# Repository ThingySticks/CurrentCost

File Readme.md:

Connect Photon/Electron to a CurrentCost unit via the RJ45 interface underneat and replace the NetSmart

Pin outs:

1 Vcc supply
4 GND
7 EnviR Unit Rx Data
8 EnviR Unit Tx Data

Data:

<msg>          
   <src>CC128-v0.11</src> 
   <dsb>00089</dsb>     
   <time>13:02:39</time>     
   <tmpr>18.7</tmpr>        
   <sensor>1</sensor>     
   <id>01234</id>                
   <type>1</type>              
   <ch1>
      <watts>00345</watts>
   </ch1>
   <ch2>
      <watts>02151</watts>
   </ch2>
   <ch3>
      <watts>00000</watts>
   </ch3>
</msg>

Expected Serial interface:

 baudrate: 57600,
  dataBits: 8,
  parity: 'none',
  stopBits: 1

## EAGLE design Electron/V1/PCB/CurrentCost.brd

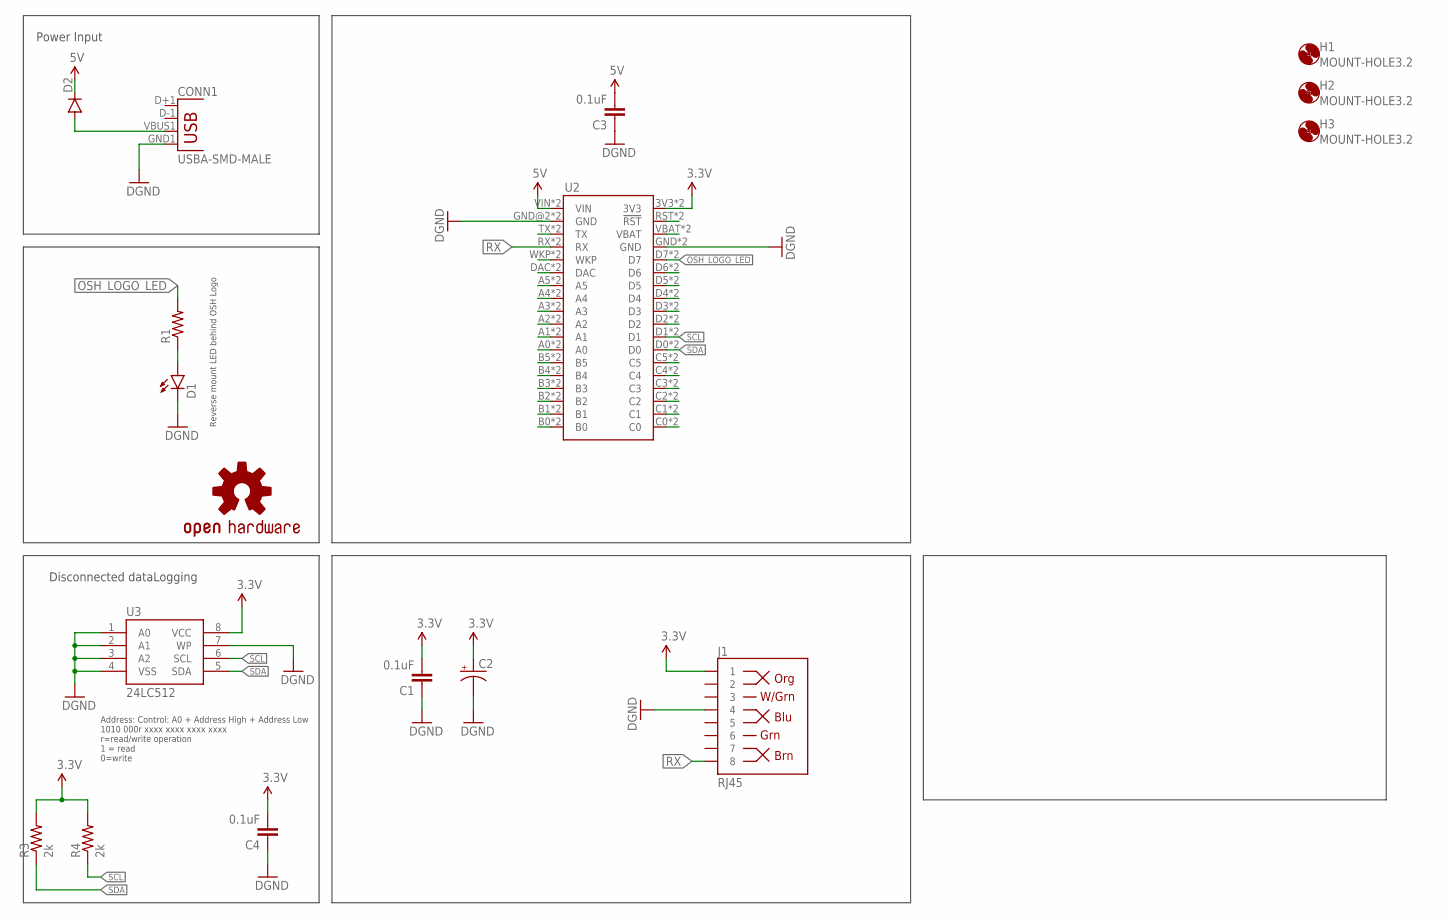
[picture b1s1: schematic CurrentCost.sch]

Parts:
C1, C3, C4: 0.1uF; 0805
C2: CAP_POLPTH1; CPOL-RADIAL-100UF-25V
CONN1: USBA-SMD-MALE; USB-A-SMT-MALE
D1: LED1206-BOTTOM; LED-1206-BOTTOM
D2: DIODESMA; SMA-DIODE
H1, H2, H3: MOUNT-HOLE3.2; 3,2
J1: RJ45; RJ45-8; FARNELL 1524544
LOGO1: OSHW-LOGOM; OSHW-LOGO-M
R1: RESISTOR1206; 1206
R3, R4: 2k; 0805
U2: ELECTRONDUALNAMED; ELECTRON_SIMPLE_SILK_NAMES_DUAL
U3: 24LC512; SO08; FARNELL 1801220

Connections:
3.3V: C1.2, C2.1 (+), C4.2, J1.1, R3.2, R4.2, U2.3V3, U2.3V3_1 (3V3), U3.8 (VCC)
5V: C3.2, D2.C, U2.VIN, U2.VIN_1B (VIN)
DQ: U2.A0, U2.A0_1 (A0)
GND: C1.1, C2.2 (-), C3.1, C4.1, CONN1.GND1 (GND), D1.C, J1.4, U2.GND, U2.GND@2 (GND), U2.GND_1 (GND), U2.GND_1B (GND), U3.1 (A0), U3.2 (A1), U3.3 (A2), U3.4 (VSS), U3.7 (WP)
MISO: U2.A4, U2.A4_1 (A4)
MOSI: U2.A5, U2.A5_1 (A5)
unnamed: CONN1.VBUS1 (VBUS), D2.A
unnamed: U2.A1, U2.A1_1 (A1)
unnamed: U2.D2, U2.D2_1 (D2)
unnamed: U2.VBAT, U2.VBATT_1 (VBAT)
unnamed: U2.RST (!RST), U2.RST_1 (!RST)
unnamed: U2.D3, U2.D3_1 (D3)
unnamed: U2.D6, U2.D6_1 (D6)
unnamed: U2.D5, U2.D5_1 (D5)
unnamed: D1.A, R1.1
unnamed: U2.C1, U2.C1_1 (C1)
unnamed: U2.C5, U2.C5_1 (C5)
unnamed: U2.C4, U2.C4_1 (C4)
unnamed: U2.C3, U2.C3_1 (C3)
unnamed: U2.C2, U2.C2_1 (C2)
unnamed: U2.C0, U2.C0_1 (C0)
unnamed: U2.D4, U2.D4_1 (D4)
unnamed: U2.B0, U2.B0_1 (B0)
unnamed: U2.B1, U2.B1_1 (B1)
unnamed: U2.B2, U2.B2_1 (B2)
unnamed: U2.B3, U2.B3_1 (B3)
unnamed: U2.B4, U2.B4_1 (B4)
unnamed: U2.B5, U2.B5_1 (B5)
unnamed: U2.WKP, U2.WKP_1 (WKP)
unnamed: U2.TX, U2.TX_1 (TX)
OSH_LOGO_LED: R1.2, U2.D7, U2.D7_1 (D7)
RX: J1.8, U2.RX, U2.RX_1 (RX)
SCK: U2.A3, U2.A3_1 (A3)
SCL: R4.1, U2.D1, U2.D1_1 (D1), U3.6 (SCL)
SDA: R3.1, U2.D0, U2.D0_1 (D0), U3.5 (SDA)
SS: U2.A2, U2.A2_1 (A2)
VIN_MONITOR: U2.DAC, U2.DAC_1 (DAC)

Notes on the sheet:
Disconnected dataLogging
Power Input
Reverse mount LED behind OSH Logo
Address: Control: A0 + Address High + Address Low
1010 000r xxxx xxxx xxxx xxxx r=read/write operation 1 = read 0=write

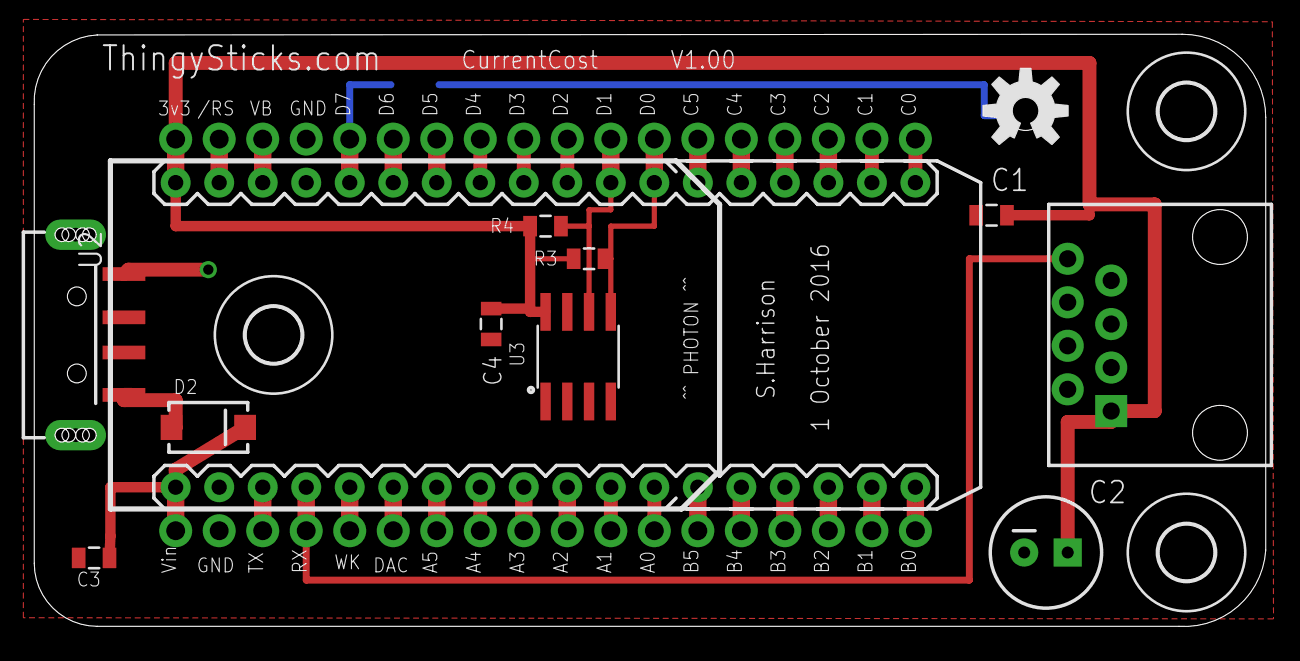
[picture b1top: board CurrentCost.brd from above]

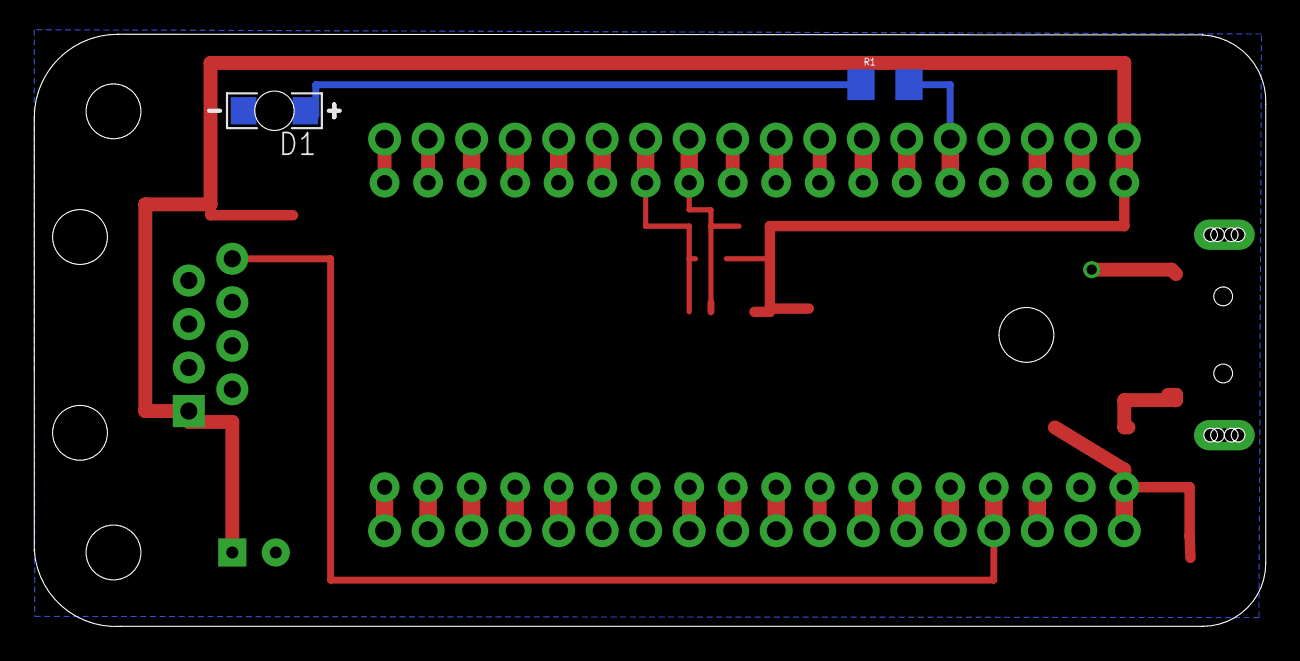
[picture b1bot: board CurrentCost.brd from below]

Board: 2 copper layers, 71.9 x 34.6 mm, 17 parts (2 on the bottom side), 37 nets.

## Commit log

2016-10-01 Initial version as send to DirtyPCBs.
2018-06-07 Improved measurements and added value for RJ45
2018-06-07 Image exports from the PCB.

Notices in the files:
parts and their libraries:
SparkFun-Connectors: Licensing: Creative Commons ShareAlike 4.0 International - https://creativecommons.org/licenses/by-sa/4.0
